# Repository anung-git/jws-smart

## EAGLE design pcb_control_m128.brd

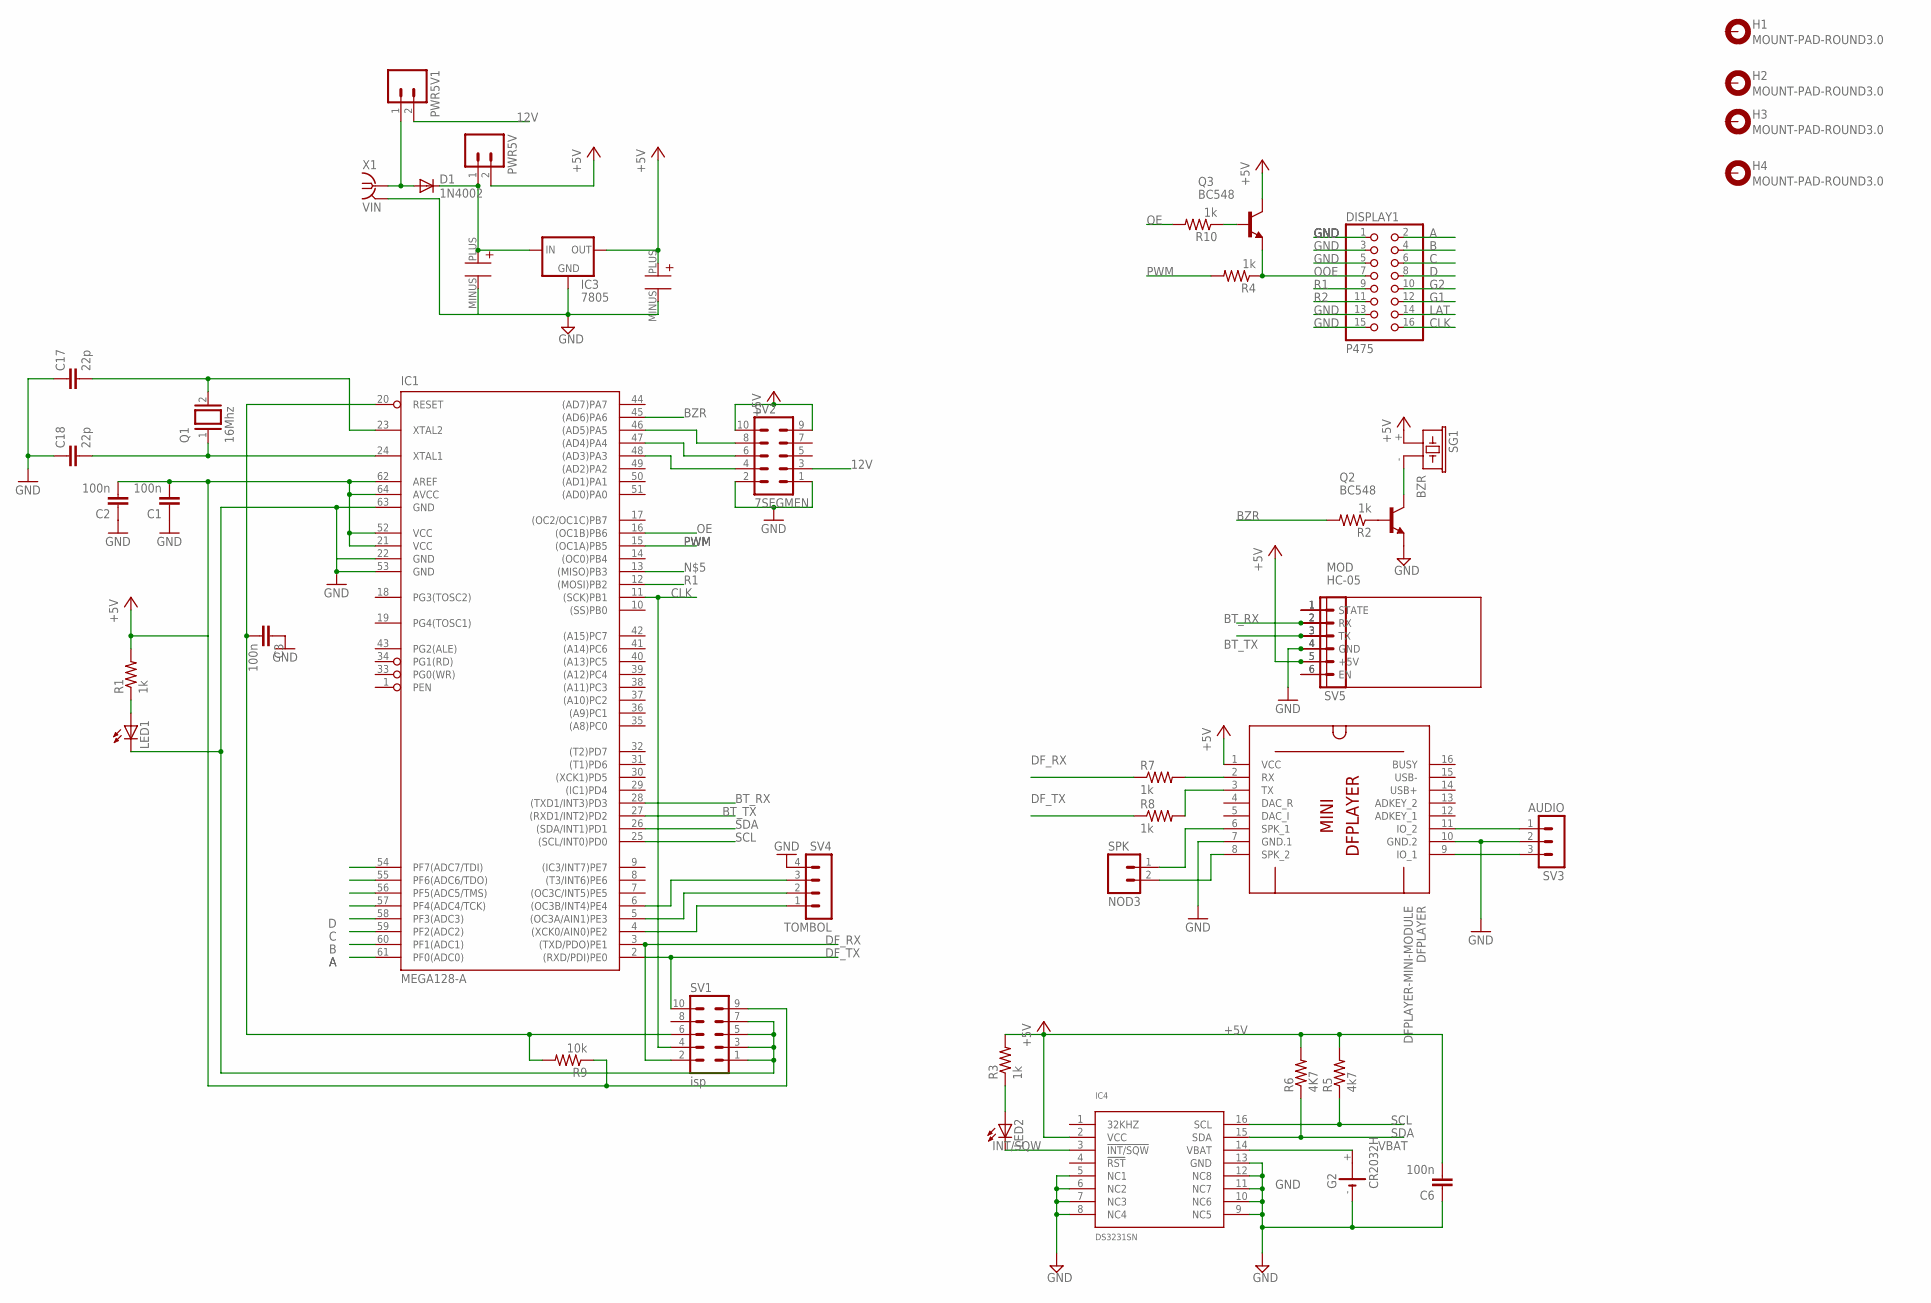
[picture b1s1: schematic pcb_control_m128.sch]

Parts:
C1, C2, C3, C6: 100n; C025-024X044
C17, C18: 22p; C025-024X044
C23: 470U; EEU-FR1C471B
C24: 1000U; EEU-FR1C471B
D1: 1N4002; DO35-10
DFPLAYER: DFPLAYER-MINI-MODULE
DISPLAY1: P475; 2X08
G2: CR2032H
H1, H2, H3, H4: MOUNT-PAD-ROUND3.0; 3,0-PAD
IC1: MEGA128-A; TQFP64
IC3: 7805; 78XXS
IC4: DS3231SN; SO16W
LED1, LED2: LED3MM
MOD: HC-05; WIRELESS-BLUETOOTH-HC-05
NOD3: SPK; 1X02
PWR5V, PWR5V1: M02PTH; 1X02
Q1: 16Mhz; QS
Q2, Q3: BC548; TO92-EBC
R1, R2, R3, R4, R7, R8, R10: 1k; AXIAL-0.3
R5: 4k7; AXIAL-0.3
R6: 4K7; AXIAL-0.3
R9: 10k; AXIAL-0.3
SG1: BZR; F/CM12P
SV1: isp; MA05-2
SV2: 7SEGMEN; MA05-2
SV3: AUDIO; MA03-1
SV4: TOMBOL; MA04-1
SV5: MA06-1
X1: VIN; J502-ND

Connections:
5VPANEL: C24.PLUS, D1.C, IC3.IN, PWR5V.1
12V: PWR5V1.2, SV2.3
12V1: D1.A, PWR5V1.1, X1.3 (1), X1.4 (1)
+5V: C1.2, C2.2, C6.2, C23.PLUS, DFPLAYER.1 (VCC), IC1.21 (VCC), IC1.52 (VCC), IC1.62 (AREF), IC1.64 (AVCC), IC3.OUT, IC4.2 (VCC), MOD.5 (+5V), PWR5V.2, Q3.C, R1.P$2 (2), R3.P$2 (2), R5.P$2 (2), R6.P$2 (2), R9.P$1 (1), SG1.+ (1), SV1.9, SV2.9, SV2.10, SV5.5
A: DISPLAY1.2, IC1.61 (PF0(ADC0))
B: DISPLAY1.4, IC1.60 (PF1(ADC1))
BT_RX: IC1.28 ((TXD1/INT3)PD3), MOD.2 (RX), SV5.2
BT_TX: IC1.27 ((RXD1/INT2)PD2), MOD.3 (TX), SV5.3
BZR: IC1.45 ((AD6)PA6), R2.P$2 (2)
C: DISPLAY1.6, IC1.59 (PF2(ADC2))
CLK: DISPLAY1.16, IC1.11 ((SCK)PB1), SV1.4
D: DISPLAY1.8, IC1.58 (PF3(ADC3))
DF_RX: IC1.3 ((TXD/PDO)PE1), R7.P$1 (1), SV1.2
DF_TX: IC1.2 ((RXD/PDI)PE0), R8.P$1 (1), SV1.10
G1: DISPLAY1.12
G2: DISPLAY1.10
GND: C1.1, C2.1, C3.1, C6.1, C17.1, C18.1, C23.MINUS, C24.MINUS, DFPLAYER.7 (GND.1), DFPLAYER.10 (GND.2), DISPLAY1.1, DISPLAY1.3, DISPLAY1.5, DISPLAY1.13, DISPLAY1.15, G2.-, IC1.22 (GND), IC1.53 (GND), IC1.63 (GND), IC3.GND, IC4.5 (NC1), IC4.6 (NC2), IC4.7 (NC3), IC4.8 (NC4), IC4.9 (NC5), IC4.10 (NC6), IC4.11 (NC7), IC4.12 (NC8), IC4.13 (GND), LED1.K (C), MOD.4 (GND), Q2.E, SV1.1, SV1.3, SV1.5, SV1.7, SV2.1, SV2.2, SV3.2, SV4.4, SV5.4, X1.2, X1.5 (2)
INT/SQW: IC4.3 (!INT/SQW), LED2.K (C)
LAT: DISPLAY1.14, IC1.57 (PF4(ADC4/TCK))
unnamed: Q2.B, R2.P$1 (1)
unnamed: Q2.C, SG1.- (2)
unnamed: LED2.A, R3.P$1 (1)
unnamed: C3.2, IC1.20 (RESET), R9.P$2 (2), SV1.6
unnamed: MOD.1 (STATE), SV5.1
unnamed: LED1.A, R1.P$1 (1)
unnamed: DFPLAYER.2 (RX), R7.P$2 (2)
unnamed: DFPLAYER.3 (TX), R8.P$2 (2)
unnamed: Q3.B, R10.P$1 (1)
unnamed: MOD.6 (EN), SV5.6
unnamed: IC1.48 ((AD3)PA3), SV2.4
unnamed: IC1.47 ((AD4)PA4), SV2.6
unnamed: IC1.46 ((AD5)PA5), SV2.8
unnamed: IC1.4 ((XCK0/AIN0)PE2), SV4.1
unnamed: IC1.5 ((OC3A/AIN1)PE3), SV4.2
unnamed: IC1.6 ((OC3B/INT4)PE4), SV4.3
unnamed: DFPLAYER.6 (SPK_1), NOD3.1
unnamed: DFPLAYER.8 (SPK_2), NOD3.2
unnamed: DFPLAYER.9 (IO_1), SV3.3
unnamed: DFPLAYER.11 (IO_2), SV3.1
unnamed: C17.2, IC1.23 (XTAL2), Q1.2
unnamed: C18.2, IC1.24 (XTAL1), Q1.1
OE: IC1.16 ((OC1B)PB6), R10.P$2 (2)
OOE: DISPLAY1.7, Q3.E, R4.P$1 (1)
PWM: IC1.15 ((OC1A)PB5), R4.P$2 (2)
R1: DISPLAY1.9, IC1.12 ((MOSI)PB2)
R2: DISPLAY1.11
SCL: IC1.25 ((SCL/INT0)PD0), IC4.16 (SCL), R5.P$1 (1)
SDA: IC1.26 ((SDA/INT1)PD1), IC4.15 (SDA), R6.P$1 (1)
VBAT: G2.+, IC4.14 (VBAT)

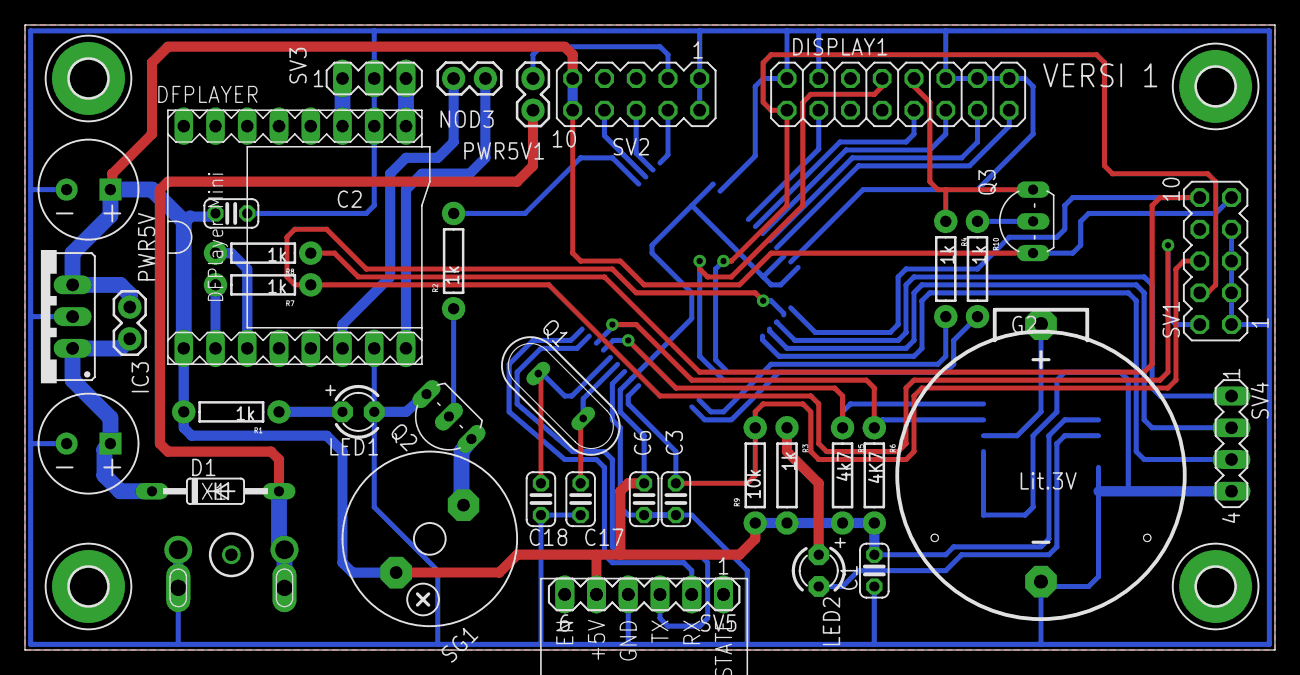
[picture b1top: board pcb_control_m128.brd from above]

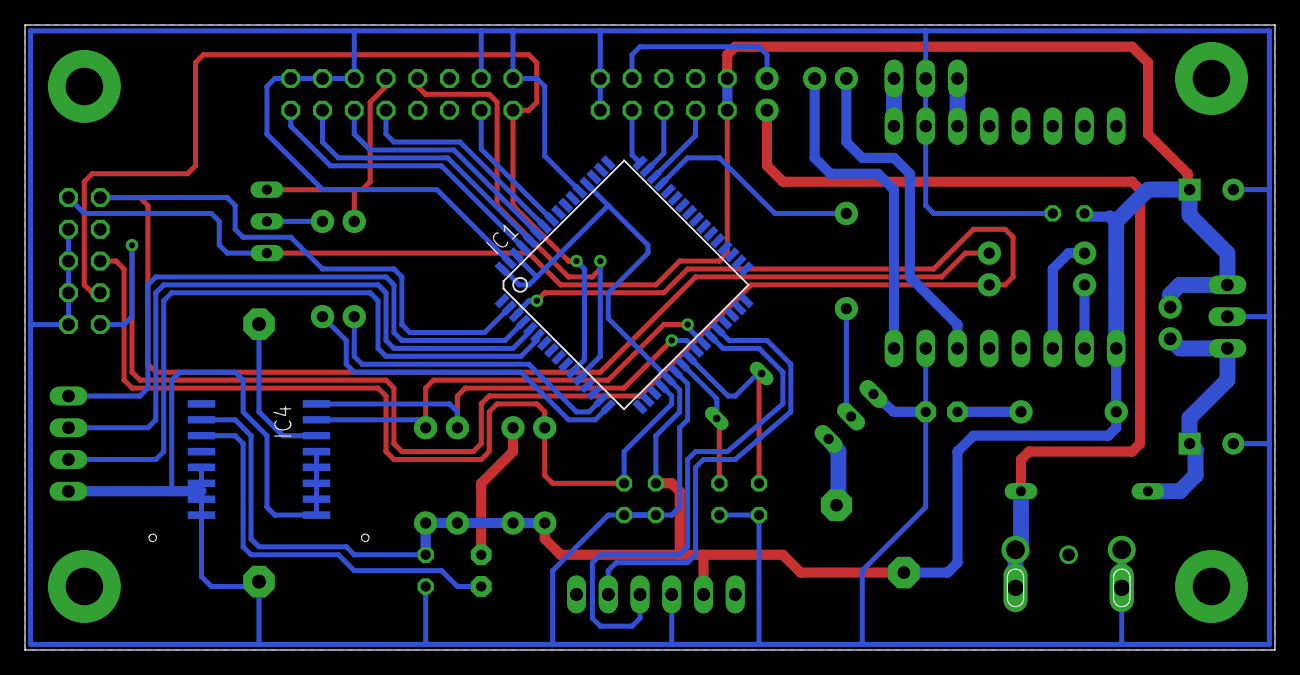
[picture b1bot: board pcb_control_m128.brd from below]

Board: 2 copper layers, 100.0 x 50.0 mm, 45 parts (2 on the bottom side), 46 nets.

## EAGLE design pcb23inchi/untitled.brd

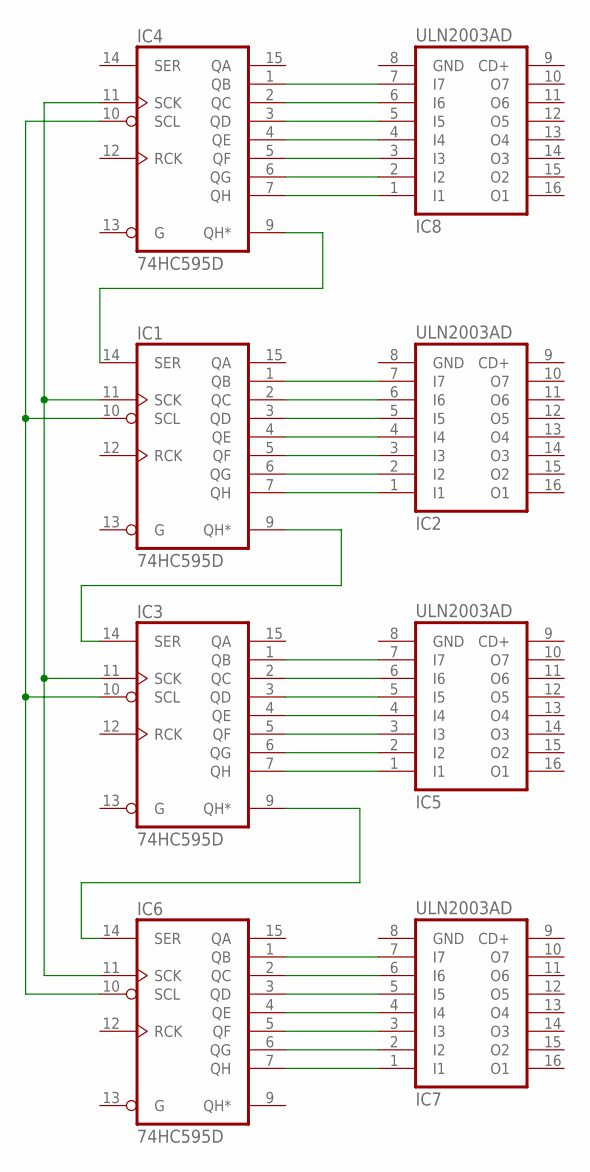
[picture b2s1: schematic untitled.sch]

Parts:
IC1, IC3, IC4, IC6: 74HC595D; SO16
IC2, IC5, IC7, IC8: ULN2003AD; SO16

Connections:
GND: IC1.8 (GND), IC2.8 (GND), IC3.8 (GND), IC4.8 (GND), IC5.8 (GND), IC6.8 (GND), IC7.8 (GND), IC8.8 (GND)
unnamed: IC4.7 (QH), IC8.1 (I1)
unnamed: IC4.6 (QG), IC8.2 (I2)
unnamed: IC4.5 (QF), IC8.3 (I3)
unnamed: IC4.4 (QE), IC8.4 (I4)
unnamed: IC4.3 (QD), IC8.5 (I5)
unnamed: IC4.2 (QC), IC8.6 (I6)
unnamed: IC4.1 (QB), IC8.7 (I7)
unnamed: IC1.7 (QH), IC2.1 (I1)
unnamed: IC1.6 (QG), IC2.2 (I2)
unnamed: IC1.5 (QF), IC2.3 (I3)
unnamed: IC1.4 (QE), IC2.4 (I4)
unnamed: IC1.3 (QD), IC2.5 (I5)
unnamed: IC1.2 (QC), IC2.6 (I6)
unnamed: IC1.1 (QB), IC2.7 (I7)
unnamed: IC3.7 (QH), IC5.1 (I1)
unnamed: IC3.6 (QG), IC5.2 (I2)
unnamed: IC3.5 (QF), IC5.3 (I3)
unnamed: IC3.4 (QE), IC5.4 (I4)
unnamed: IC3.3 (QD), IC5.5 (I5)
unnamed: IC3.2 (QC), IC5.6 (I6)
unnamed: IC3.1 (QB), IC5.7 (I7)
unnamed: IC6.7 (QH), IC7.1 (I1)
unnamed: IC6.6 (QG), IC7.2 (I2)
unnamed: IC6.5 (QF), IC7.3 (I3)
unnamed: IC6.4 (QE), IC7.4 (I4)
unnamed: IC6.3 (QD), IC7.5 (I5)
unnamed: IC6.2 (QC), IC7.6 (I6)
unnamed: IC6.1 (QB), IC7.7 (I7)
unnamed: IC1.10 (SCL), IC3.10 (SCL), IC4.10 (SCL), IC6.10 (SCL)
unnamed: IC1.11 (SCK), IC3.11 (SCK), IC4.11 (SCK), IC6.11 (SCK)
unnamed: IC1.14 (SER), IC4.9 (QH*)
unnamed: IC1.9 (QH*), IC3.14 (SER)
unnamed: IC3.9 (QH*), IC6.14 (SER)
VCC: IC1.16 (VCC), IC3.16 (VCC), IC4.16 (VCC), IC6.16 (VCC)

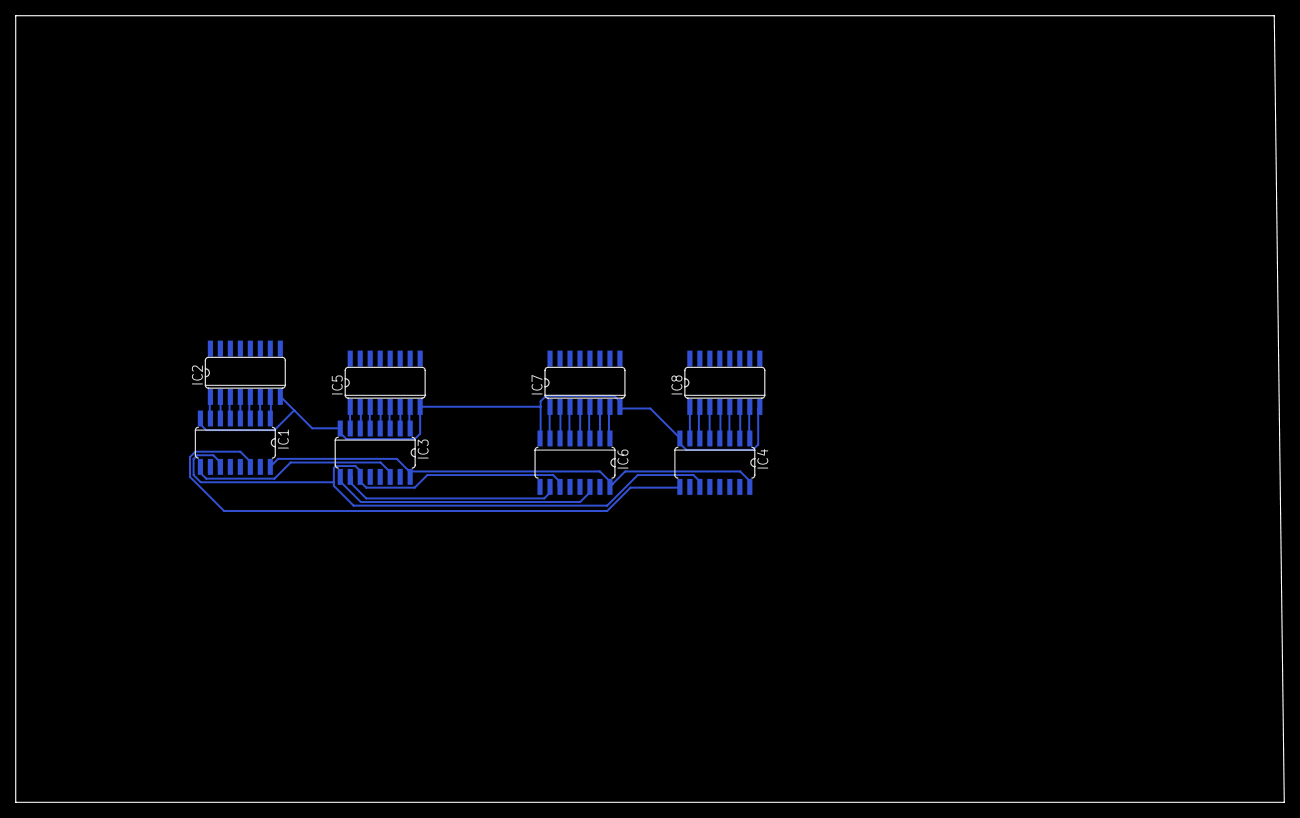
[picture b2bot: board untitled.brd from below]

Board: 2 copper layers, 161.3 x 100.0 mm, 8 parts (8 on the bottom side), 35 nets.

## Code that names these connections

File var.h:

#define set_data_segmen() { PORTA |= _BV(PA5); }
#define clear_data_segmen() { PORTA &= ~_BV(PA5); }

#define clock_data_segmen() { PORTA |= _BV(PA6); PORTA &= ~_BV(PA6);}

#define set_strobe_segmen() { PORTA |= _BV(PA4); }
#define clear_strobe_segmen() { PORTA &= ~_BV(PA4); }

#define buzer  2  

#define set_buzer() { PORTE |= _BV(PE2); }
#define clear_buzer() { PORTE &= ~_BV(PE2); }

#define strobePin  40 //Pin connected to Strobe (pin 1) of 4094
#define dataPin  39 //Pin connected to Data (pin 2) of 4094
#define clockPin  38  //Pin connected to Clock (pin 3) of 4094

#define tombol_up 5
#define tombol_menu 45
#define tombol_down 46

//byte segChar[] = {1, 2, 4, 8, 16, 32, 64, 128, 255, 0}; //cek

byte sqw;
unsigned long previousMillis = 0;  
const byte data_jam[]= {136 ,238 ,73 ,76 ,46 ,28 ,24 ,206 ,8 ,12 ,255};
const byte data_kalender []={129 ,237 ,67 ,73 ,45 ,25 ,17 ,205 ,1 ,9 ,255};
const byte data_jadwal []={129 ,237 ,67 ,73 ,45 ,25 ,17 ,205 ,1 ,9 ,255};

//===============================================================================
//seting
volatile static byte commad;

#define text_iq_subuh 100
#define text_iq_duhur 200
#define text_iq_ashar 300
#define text_iq_maghrib 400
#define text_iq_isya 500
#define text_iq_jumat 600
#define text_run 700

#define command_start 1
#define set_jam 2
#define set_text 3
#define set_iqomah 4
#define set_tarhim 5
#define set_brightnes 6
#define set_offsite 7
#define set_fix 8
#define set_bt_kota 9
#define set_adzan 10
#define play_mp3 11
#define command_end 12
volatile static byte command;



struct MyObject{
    int  kota;
    byte  beep;
    byte  timer_adzan_subuh ;
    byte  timer_adzan_duhur ;
    byte  timer_adzan_ashar ;
    byte  timer_adzan_maghrib ;
    byte  timer_adzan_isya ;
    byte  timer_adzan_jumat ;
    
    byte  iqomah_subuh ;
    byte  iqomah_duhur ;
    byte  iqomah_ashar  ;
    byte  iqomah_maghrib ;
    byte  iqomah_isya ;
    byte  iqomah_jumat ;
    
    byte  lama_sholat_subuh ;
    byte  lama_sholat_duhur ;
    byte  lama_sholat_ashar  ;
    byte  lama_sholat_maghrib ;
    byte  lama_sholat_isya ;
    byte  lama_sholat_jumat ;
    byte  tartil_subuh ;// 0= mati dan >0 hidup
    byte  tartil_duhur ;
    byte  tartil_ashar ;
    byte  tartil_maghrib; 
    byte  tartil_isya ;
    byte  tartil_jumat ;
    byte  kecerahan_1 ;
    byte  kecerahan_2 ;
    byte  kecerahan_3 ;
    byte  kecerahan_4 ;
    int  jam_kecerahan_1 ;
    int  jam_kecerahan_2 ;
    int  jam_kecerahan_3 ;
    int  jam_kecerahan_4 ;
    int  tambah_kurang_subuh ;
    int  tambah_kurang_duhur ;
    int  tambah_kurang_ashar ; 
    int  tambah_kurang_maghrib ; 
    int  tambah_kurang_isya ;
    int  jadwal_fix_subuh ;
    int  jadwal_fix_duhur ;
    int  jadwal_fix_ashar ;
    int  jadwal_fix_maghrib ;
    int  jadwal_fix_isya ;
    byte  mazhab_ashar  ;
    int  set_kota_gmt ;
    float  set_kota_lnt ;
    float  set_kota_bjr ;
};


#define detik 0
#define menit 1
#define jam 2
#define hari 3
#define tanggal 4
#define bulan 5
#define tahun 6
#define waktu_imsya 7
#define waktu_subuh 8
#define waktu_duhur 9
#define waktu_ashar 10
#define waktu_magrib 11
#define waktu_isya 12
#define waktu_jumat 13
#define display_off 14

#define jadwal 14
#define all 15

#define senin 1
#define selasa 2
#define rabu 3
#define kamis 4
#define jumat 5
#define sabtu 6
#define ahad 7
#define alarm_beep 8
#define on 9
#define off 10
#define imsya 11
#define subuh 12
#define duhur 13
#define ashar 14
#define magrib 15
#define isya 16
#define stanbay 17
#define iqomah 18
#define set_kota 19
#define jadwal 20
#define tlwh_1 21
#define tlwh_2 22
#define tlwh_3 23
#define tlwh_4 24
#define tlwh_5 25
#define tlwh_6 26
#define kutbah 27


#define ka   65
#define kb   49
#define kd   97
#define ke   3
#define kf   23
#define kg   9
#define kh   53
#define ki   237
#define kj   225
#define kk   21
#define kl   179
#define km1  135
#define km2  141
#define kn   133
#define ko   129
#define kp   7
#define kq   13
#define kr   151
#define ks   25
#define kt   51
#define ku   161
#define ky   41
#define kw1  177
#define kw2  225
#define k_   255

const PROGMEM  uint8_t dataKalender []={
  k_,ks,ke,kn,ki,kn,k_,k_,
  k_,ks,ke,kl,ka,ks,ka,k_,
  k_,k_,kr,ka,kb,ku,k_,k_,
  k_,kk,ka,km1,km2,ki,ks,k_,
  k_,kj,ku,km1,km2,ka,kt,k_,
  k_,ks,ka,kb,kt,ku,k_,k_,
  k_,k_,ka,kh,ka,kd,k_,k_,
  k_,ka,kl,ka,kr,km1,km2,k_,
  k_,k_,k_,ko,kn,k_,k_,k_,
  k_,k_,k_,ko,kf,kf,k_,k_,
  k_,kt,ke,kr,kb,ki,kt,k_,
  k_,k_,ks,ku,kb,ku,kh,k_,
  k_,k_,kd,ku,kh,ku,kr,k_,
  k_,k_,ka,ks,kh,ka,kr,k_,
  km1,km2,ka,kg,kh,kr,ki,kb,
  k_,k_,ki,ks,ky,ka,k_,k_,
  k_,ks,kt,ka,kn,kb,ky,k_,
  ki,kq,ko,km1,km2,ka,kh,k_,
  k_,k_,kk,ko,kt,ka,k_,k_,
  k_,kj,ka,kd,kw1,kw2,ka,kl,
  kt,ka,kr,kt,ki,kl,k_,data_kalender[1],
  kt,ka,kr,kt,ki,kl,k_,data_kalender[2],
  kt,ka,kr,kt,ki,kl,k_,data_kalender[3],
  kt,ka,kr,kt,ki,kl,k_,data_kalender[4],
  kt,ka,kr,kt,ki,kl,k_,data_kalender[5],
  kt,ka,kr,kt,ki,kl,k_,data_kalender[6],
  kk,kh,ku,kt,kb,ka,kh,k_,
  k_,k_,k_,k_,k_,k_,k_,k_,
};

int data[20];

volatile unsigned char segmen[36];
unsigned char hidup,mati;

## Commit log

2019-07-16 smart lama
2019-09-18 tambah file eprom
2019-09-18 hapus fitur tambah kurang dan fix jadwal
2019-09-18 hapus hex lama
2019-09-18 file test lib jadwal
2019-09-28 tambah fitur reset
2019-09-28 ganti bt
2019-09-28 remove debug
2019-09-29 set kota = 0 ketika setting bt
2019-10-12 type jws suruq
2019-10-23 ubah suruq -> terbit
2019-10-23 bug terbit
2019-10-23 compile

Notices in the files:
parts and their libraries:
diy-modules: Released under the Creative Commons Attribution 4.0 International License: http://creativecommons.org/licenses/by/4.0
SparkFun-Passives: Licensing: Creative Commons ShareAlike 4.0 International - https://creativecommons.org/licenses/by-sa/4.0
